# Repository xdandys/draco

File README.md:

Draco
==========

Draco is opensource HW&SW UAV flight controller board. It was primary designed for my needs, but anybody can manufacture it, use it or modify it. If you would like to own one, you can contact me. 

It has two MCUs on it. The smaller one is used for OSD. The bigger one is running [TauLabs][1] flight code.

###Features###
* main MCU STM32F4, MCU for OSD STM32F303CC
* 32MBit serial flash
* MPU9250 in SPI mode
* MS5611 in SPI mode
* CAN bus transceiver
* microSD slot via SDIO
* 4x A/D inputs
* slot for telemetry module (XBee or PirateBee)
* half-duplex inverted serial line for new FrSky S.PORT telemetry bus
* GPS port with power, UART and I2C for external compass
* 2x extension port with UART/I2C and GPIOs
* extension SPI port
* dedicated sonar port with power and trigger+echo signals
* microUSB
* 12x PWM in/out + 1x S.BUS/CPPM pin on 2.54mm header
* 6x LEDs
* micro button
* OSD with resolution 320x240, automatic PAL/NTSC detection
* dimmensions: 62x47mm

###TauLabs###
Draco is currently one of the non-official TauLabs target. You can find ported code at [my fork][2]. There are still some things missing and I will probably add them in short time:

* support for microSD card logging
* support of FrSky S.PORT telemetry protocol
* micro button support

  [1]: http://taulabs.org/
  [2]: https://github.com/strnadda/TauLabs/tree/draco

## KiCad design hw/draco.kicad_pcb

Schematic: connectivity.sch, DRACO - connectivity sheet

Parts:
C1, C3, C5, C7, C8, C10, C12, C14, C15, C17, C43, C47, C48: 100nF; c_0603
C2, C4: 4.7uF; c_0805
C6, C13: 10uF; c_0805
C9: 1uF; c_0805
C11: 10nF; c_0603
C16: 22uF; c_0805
C18: 56nF; c_0603
C44: 510pF; c_0603
D1: PMEG6010CEH
D2: LED_RED; led_2.1x0.6
D3: LED_ORANGE; led_2.1x0.6
D4: LED_BLUE; led_2.1x0.6
D5: LED_GREEN; led_2.1x0.6
D9: MBRS130T3G
D10: 1SMB7.0AT3G
G1, G2, G3, G4, G5: DUMMY
L1: 10uH; r_0805
P1: CONN_13X3; pin_strip_13x3-90
P2, P3, P5, P7, P8, P9: CONN_4; picoblade_4-90
P4: MICROUSB; conn_usb_B_micro_smd-FCI
P6, P13: CONN_6; picoblade_6-90
P10: MICROSD; MICRO-SD-SOCKET-PP
P11: CONN_9; picoblade_9-90
P12: CONN_2; picoblade_2-90
P19, P20, P21, P22: CONN_1; 1pin
Q2: NTA4153NT1G
Q3: NTA4151PT1G
Q4, Q5, Q6, Q7: PDTC114EE; sc75
R1, R2, R3, R4, R5, R6, R7, R8, R9, R10, R11, R12, R13, R14, R25, R26, R33, R42, R43, R46, R48, R49, R50, R51, R63, R64, R65: 470R; r_0603
R15, R16: 22R; r_0603
R17: 120R; r_0805
R18, R19, R20, R21, R24, R29, R30, R66, R67: 39k; r_0603
R22: 82k; r_0603
R23: 12k; r_0603
R27, R28, R31, R32, R53, R60: 220R; r_0603
R34, R36, R37, R38: 39k; r_0402
R35: 1M; r_0402
R39: 681k; r_0603
R40, R41: 4.7k; r_0603
R44, R58, R59: 4k7; r_0603
R45, R47: 330R; r_0603
R52: 180R; r_0603
R68, R69: 75R; r_0603
R70: 390R; r_0603
R71: 620R; r_0603
SW1: STG719; sot23-6
U1: XBEE; xbee-smt
U2: LTC4411; sot23-5
U3: SN65HVD233; so-8
U4: ADP3338AKCZ-3.3; stabil_sot223_1
U5: LT1761-3.3; tsot-5
U6: EL1883; so-8
U11: SN74AHC1G86
U12: MAX4090

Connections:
+3.3V: C1.2, C3.1, C4.1, C6.1, C14.2, C16.1, C17.2, C43.2, C48.1, P10.4, Q3.2 (S), R34.2, R36.2, R37.2, R38.2, R40.2, R41.2, R44.2, R58.2, R59.2, R70.2, SW1.2 (Vcc), U1.1, U3.3 (Vcc), U4.OUT, U6.8 (Vdd), U11.5 (Vcc), U12.4 (Vcc), U12.5 (~SD); also elsewhere on the board
+3.3VADC: C11.1, C13.1, U5.5 (OUT); also elsewhere on the board
+5V: D9.1 (A), P1.2, P1.5, P1.8, P1.11, P1.14, P1.17, P1.20, P1.23, P1.26, P1.29, P1.32, P1.35, P1.38, P2.4, P3.4, P6.1, P7.4, P11.9, P13.1, R45.2, R47.2, R52.2, R53.2
AD0: C5.2, R22.2, R23.2; also elsewhere on the board
AD1: C7.2, R21.2, R24.2; also elsewhere on the board
AD2: C8.2, R20.2, R29.2; also elsewhere on the board
AD3: C10.2, R19.2, R30.2; also elsewhere on the board
CAN_RX: U3.4 (R); also elsewhere on the board
CAN_TX: U3.1 (D); also elsewhere on the board
EXTGPIO1: R65.2; also elsewhere on the board
EXTGPIO2: R64.2; also elsewhere on the board
EXTGPIO3: R63.2; also elsewhere on the board
EXTI2C_SCL: R27.2; also elsewhere on the board
EXTI2C_SDA: R28.2; also elsewhere on the board
EXTSPI_CS: R51.1; also elsewhere on the board
EXTSPI_MISO: R49.1; also elsewhere on the board
EXTSPI_MOSI: R48.1; also elsewhere on the board
EXTSPI_SCK: R50.1; also elsewhere on the board
EXTUART1_RX: R43.2; also elsewhere on the board
EXTUART1_TX: R42.2; also elsewhere on the board
EXTUART2_RX: R31.2, R58.1; also elsewhere on the board
EXTUART2_TX: R59.1, R60.2; also elsewhere on the board
F4_NRST: C12.2, P9.2; also elsewhere on the board
F4_SWCLK: P9.4; also elsewhere on the board
F4_SWDIO: P9.3; also elsewhere on the board
GND: C1.1, C2.2, C3.2, C4.2, C5.1, C6.2, C7.1, C8.1, C9.2, C10.1, C12.1, C13.2, C14.1, C16.2, C17.1, C18.1, C43.1, C44.1, C48.2, D10.1 (A), P1.1, P1.4, P1.7, P1.10, P1.13, P1.16, P1.19, P1.22, P1.25, P1.28, P1.31, P1.34, P1.37, P2.3, P3.3, P4.5, P6.2, P7.3, P8.1, P8.4, P9.1, P10.6, P10.GND, P11.8, P12.1, P13.2, Q2.2 (S), Q4.2 (E), Q5.2 (E), Q6.2 (E), Q7.2 (E), R23.1, R24.1, R29.1, R30.1, R35.1, R39.1, R66.1, R67.2, R68.1, SW1.3 (GND), U1.10, U2.2 (GND), U3.2 (GND), U3.8 (RS), U4.GND, U5.2 (GND), U6.4 (GND), U11.3 (Gnd), U12.2 (GND); also elsewhere on the board
GPS_RX: R25.2; also elsewhere on the board
GPS_TX: R26.2; also elsewhere on the board
LED_BLUE: Q6.1 (B); also elsewhere on the board
LED_GREEN: Q7.1 (B); also elsewhere on the board
LED_ORANGE: Q5.1 (B); also elsewhere on the board
LED_RED: Q4.1 (B); also elsewhere on the board
unnamed: C47.1, U12.3 (IN)
unnamed: R69.2, U12.1 (OUT), U12.6 (FB)
unnamed: C47.2, P8.3, R68.2
unnamed: P11.6, R64.1
unnamed: P11.7, R65.1
unnamed: D5.2 (K), Q7.3 (C)
unnamed: P1.3, R66.2, U11.1 (IN1)
unnamed: C15.2, U6.2 (COMP_IN)
unnamed: C15.1, C44.2, R71.1
unnamed: P8.2, SW1.5 (D)
unnamed: R69.1, R71.2, SW1.6 (S2)
unnamed: C2.1, D1.2 (K), D9.2 (K), D10.2 (K), L1.1, U2.5 (OUT), U4.IN
unnamed: P11.1, R42.1
unnamed: P5.1, R19.1
unnamed: P11.5, R63.1
unnamed: P11.2, R43.1
unnamed: P5.3, R21.1
unnamed: P5.4, R22.1
unnamed: P5.2, R20.1
unnamed: C11.2, U5.4 (BYP)
unnamed: P6.6, R25.1
unnamed: P6.5, R26.1
unnamed: P6.3, P11.4, R28.1, R40.1
unnamed: D1.1 (A), P4.1, R18.2, U2.1 (IN)
unnamed: C9.1, L1.2, U5.1 (IN)
unnamed: P4.2, R15.1
unnamed: P4.3, R16.1
unnamed: P3.1, R1.1
unnamed: P3.2, R2.1
unnamed: P2.2, R17.1, U3.6 (CANL)
unnamed: P2.1, R17.2, U3.7 (CANH)
unnamed: P1.18, R10.1
unnamed: P1.15, R11.1
unnamed: P1.12, R12.1
unnamed: P1.6, R14.1
unnamed: P1.36, R4.1
unnamed: P1.33, R5.1
unnamed: P1.30, R6.1
unnamed: P13.3, R51.2
unnamed: P1.24, R8.1
unnamed: P1.27, R7.1
unnamed: P1.21, R9.1
unnamed: P7.1, R60.1
unnamed: C18.2, R39.2, U6.6 (RSET)
unnamed: P7.2, R31.1
unnamed: P1.39, R3.1
unnamed: P6.4, P11.3, R27.1, R41.1
unnamed: P1.9, R13.1
unnamed: Q2.1 (G), Q3.3 (D), R46.1, R67.1
unnamed: P12.2 (PM), R46.2
unnamed: P13.6, R48.2
unnamed: P13.5, R49.2
unnamed: P13.4, R50.2
unnamed: R32.1, R33.1, R70.1, SW1.4 (S1)
unnamed: D2.1 (A), R45.1
unnamed: D4.1 (A), R52.1
unnamed: D3.1 (A), R47.1
unnamed: D3.2 (K), Q5.3 (C)
unnamed: D4.2 (K), Q6.3 (C)
unnamed: D2.2 (K), Q4.3 (C)
unnamed: D5.1 (A), R53.1
OSD_HSYNC: U6.7 (~HSYNC~); also elsewhere on the board
OSD_MISO_MASK: SW1.1 (SW); also elsewhere on the board
OSD_MOSI_VOUT: R32.2; also elsewhere on the board
OSD_SYNCOUT: R33.2; also elsewhere on the board
OSD_VSYNC: U6.3 (~VSYNC~); also elsewhere on the board
PWM1: R14.2; also elsewhere on the board
PWM2: R13.2; also elsewhere on the board
PWM3: R12.2; also elsewhere on the board
PWM4: R11.2; also elsewhere on the board
PWM5: R10.2; also elsewhere on the board
PWM6: R9.2; also elsewhere on the board
PWM7: R8.2; also elsewhere on the board
PWM8: R7.2; also elsewhere on the board
PWM9: R6.2; also elsewhere on the board
PWM10: R5.2; also elsewhere on the board
PWM11: R4.2; also elsewhere on the board
PWM12: R3.2; also elsewhere on the board
SBUS: U11.4 (OUT); also elsewhere on the board
SBUS_UART_INVERT: U11.2 (IN2); also elsewhere on the board
SDIO_CLK: P10.5; also elsewhere on the board
SDIO_CMD: P10.3, R36.1; also elsewhere on the board
SDIO_D0: P10.7, R37.1; also elsewhere on the board
SDIO_D1: P10.8, R38.1; also elsewhere on the board
SDIO_D2: P10.1, R34.1; also elsewhere on the board
SDIO_D3: P10.2, R35.2; also elsewhere on the board
SON_ECHO: R1.2; also elsewhere on the board
SON_TRIG: R2.2; also elsewhere on the board
SPORT_RX: Q2.3 (D), R44.1; also elsewhere on the board
SPORT_TX: Q3.1 (G); also elsewhere on the board
USBDM: R15.2; also elsewhere on the board
USBDP: R16.2; also elsewhere on the board
USBVB: R18.1; also elsewhere on the board
USB_ID: P4.4; also elsewhere on the board
XBEE_CTS: U1.12; also elsewhere on the board
XBEE_RX: U1.2; also elsewhere on the board
XBEE_TX: U1.3; also elsewhere on the board

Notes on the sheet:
Sonar
CAN bus
Extension port
GPS
SWD
S.PORT / S.BUS 2.0
SPI
LED front panel
OSD
VID_OUT VID_IN
UART_F3
Can be potentionaly fitted for I2C
Mechanical mount holes and drawings
Sync-tip clamp
LTC1411 alternative

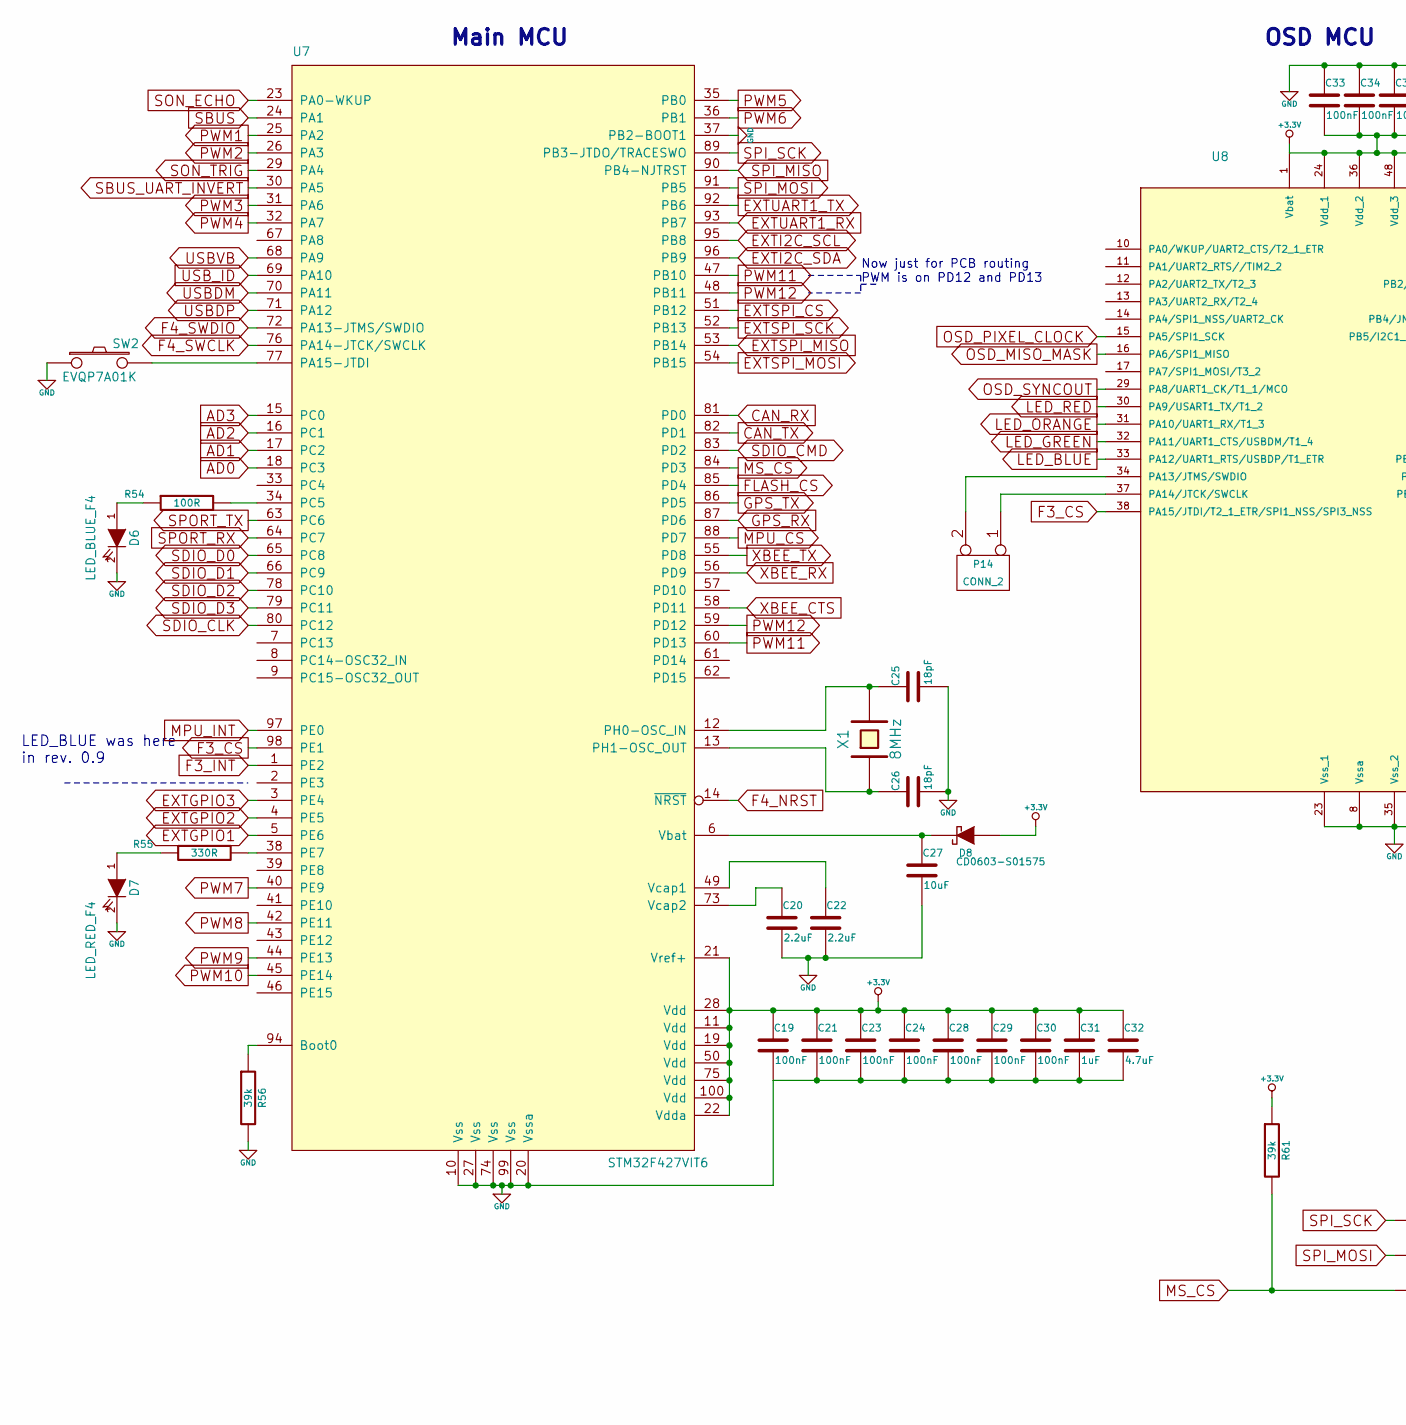
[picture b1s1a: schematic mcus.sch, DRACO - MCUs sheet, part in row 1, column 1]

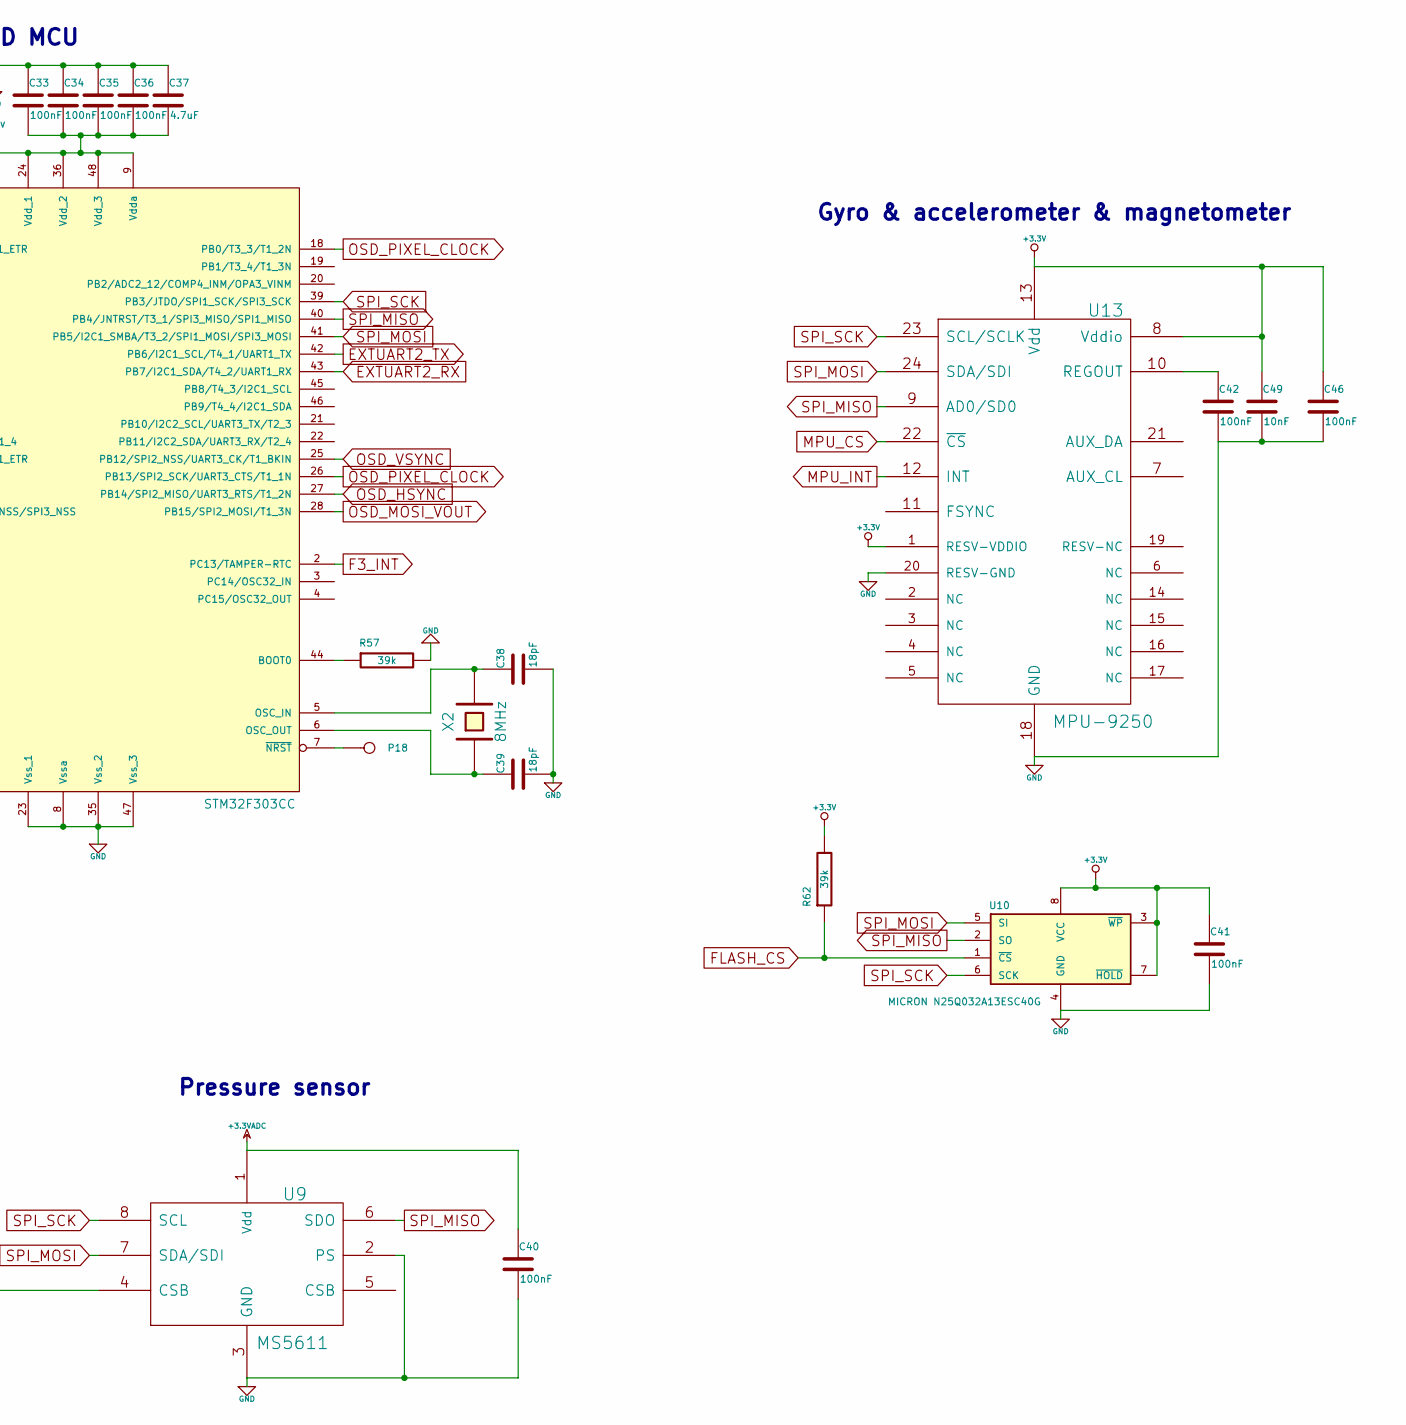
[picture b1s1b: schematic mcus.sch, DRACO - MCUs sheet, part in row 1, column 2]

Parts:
C19, C21, C23, C24, C28, C29, C30, C33, C34, C35, C36, C40, C41, C42, C46: 100nF; c_0603
C20, C22: 2.2uF; c_0805
C25, C26, C38, C39: 18pF; c_0603
C27: 10uF; c_0805
C31: 1uF; c_0603
C32: 4.7uF; c_0805
C37: 4.7uF; c_0603
C49: 10nF; c_0603
D6: LED_BLUE_F4; Led_0603
D7: LED_RED_F4; Led_0603
D8: CD0603-S01575; r_0603
P14: CONN_2
P18: CONN_1; testpoint_pad
R54: 100R; r_0603
R55: 330R; r_0603
R56, R57, R61, R62: 39k; r_0603
SW2: EVQP7A01K
U7: STM32F427VIT6; TQFP-100
U8: STM32F303CC; lqfp48
U9: MS5611
U10: MICRON N25Q032A13ESC40G
U13: MPU-9250
X1, X2: 8MHz; crystal_smd_5x3.2mm

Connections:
+3.3V: C19.1, C21.1, C23.1, C24.1, C28.1, C29.1, C30.1, C31.1, C32.1, C33.2, C34.2, C35.2, C36.2, C37.2, C41.1, C46.1, C49.1, D8.1 (A), R61.1, R62.2, U7.11 (Vdd), U7.19 (Vdd), U7.21 (Vref+), U7.22 (Vdda), U7.28 (Vdd), U7.50 (Vdd), U7.75 (Vdd), U7.100 (Vdd), U8.1 (Vbat), U8.9 (Vdda), U8.24 (Vdd_1), U8.36 (Vdd_2), U8.48 (Vdd_3), U10.3 (~WP), U10.7 (~HOLD), U10.8 (VCC), U13.1 (RESV-VDDIO), U13.8 (Vddio), U13.13 (Vdd); also elsewhere on the board
+3.3VADC: C40.1, U9.1 (Vdd); also elsewhere on the board
AD0: U7.18 (PC3); also elsewhere on the board
AD1: U7.17 (PC2); also elsewhere on the board
AD2: U7.16 (PC1); also elsewhere on the board
AD3: U7.15 (PC0); also elsewhere on the board
CAN_RX: U7.81 (PD0); also elsewhere on the board
CAN_TX: U7.82 (PD1); also elsewhere on the board
EXTGPIO1: U7.5 (PE6); also elsewhere on the board
EXTGPIO2: U7.4 (PE5); also elsewhere on the board
EXTGPIO3: U7.3 (PE4); also elsewhere on the board
EXTI2C_SCL: U7.95 (PB8); also elsewhere on the board
EXTI2C_SDA: U7.96 (PB9); also elsewhere on the board
EXTSPI_CS: U7.51 (PB12); also elsewhere on the board
EXTSPI_MISO: U7.53 (PB14); also elsewhere on the board
EXTSPI_MOSI: U7.54 (PB15); also elsewhere on the board
EXTSPI_SCK: U7.52 (PB13); also elsewhere on the board
EXTUART1_RX: U7.93 (PB7); also elsewhere on the board
EXTUART1_TX: U7.92 (PB6); also elsewhere on the board
EXTUART2_RX: U8.43 (PB7/I2C1_SDA/T4_2/UART1_RX); also elsewhere on the board
EXTUART2_TX: U8.42 (PB6/I2C1_SCL/T4_1/UART1_TX); also elsewhere on the board
F3_CS: U7.98 (PE1), U8.38 (PA15/JTDI/T2_1_ETR/SPI1_NSS/SPI3_NSS)
F3_INT: U7.1 (PE2), U8.2 (PC13/TAMPER-RTC)
F4_NRST: U7.14 (~NRST~); also elsewhere on the board
F4_SWCLK: U7.76 (PA14-JTCK/SWCLK); also elsewhere on the board
F4_SWDIO: U7.72 (PA13-JTMS/SWDIO); also elsewhere on the board
FLASH_CS: R62.1, U7.85 (PD4), U10.1 (~CS)
GND: C19.2, C20.2, C21.2, C22.2, C23.2, C24.2, C25.2, C26.2, C27.2, C28.2, C29.2, C30.2, C31.2, C32.2, C33.1, C34.1, C35.1, C36.1, C37.1, C38.2, C39.2, C40.2, C41.2, C42.2, C46.2, C49.2, D6.2 (K), D7.2 (K), R56.2, R57.2, SW2.1, U7.10 (Vss), U7.20 (Vssa), U7.27 (Vss), U7.37 (PB2-BOOT1), U7.74 (Vss), U7.99 (Vss), U8.8 (Vssa), U8.23 (Vss_1), U8.35 (Vss_2), U8.47 (Vss_3), U9.2 (PS), U9.3 (GND), U10.4 (GND), U13.18 (GND), U13.20 (RESV-GND); also elsewhere on the board
GPS_RX: U7.87 (PD6); also elsewhere on the board
GPS_TX: U7.86 (PD5); also elsewhere on the board
LED_BLUE: U8.33 (PA12/UART1_RTS/USBDP/T1_ETR); also elsewhere on the board
LED_GREEN: U8.32 (PA11/UART1_CTS/USBDM/T1_4); also elsewhere on the board
LED_ORANGE: U8.31 (PA10/UART1_RX/T1_3); also elsewhere on the board
LED_RED: U8.30 (PA9/USART1_TX/T1_2); also elsewhere on the board
MPU_CS: U7.88 (PD7), U13.22 (~CS~)
MPU_INT: U7.97 (PE0), U13.12 (INT)
MS_CS: R61.2, U7.84 (PD3), U9.4 (CSB)
unnamed: C20.1, U7.73 (Vcap2)
unnamed: C22.1, U7.49 (Vcap1)
unnamed: C27.1, D8.2 (K), U7.6 (Vbat)
unnamed: R57.1, U8.44 (BOOT0)
unnamed: P18.1, U8.7 (~NRST~)
unnamed: R55.2, U7.38 (PE7)
unnamed: R56.1, U7.94 (Boot0)
unnamed: C42.1, U13.10 (REGOUT)
unnamed: D7.1 (A), R55.1
unnamed: R54.2, U7.34 (PC5)
unnamed: D6.1 (A), R54.1
unnamed: SW2.2, U7.77 (PA15-JTDI)
unnamed: P14.2 (PM), U8.34 (PA13/JTMS/SWDIO)
unnamed: P14.1, U8.37 (PA14/JTCK/SWCLK)
unnamed: C39.1, U8.6 (OSC_OUT), X2.1
unnamed: C38.1, U8.5 (OSC_IN), X2.2
unnamed: C25.1, U7.12 (PH0-OSC_IN), X1.2
unnamed: C26.1, U7.13 (PH1-OSC_OUT), X1.1
OSD_HSYNC: U8.27 (PB14/SPI2_MISO/UART3_RTS/T1_2N); also elsewhere on the board
OSD_MISO_MASK: U8.16 (PA6/SPI1_MISO); also elsewhere on the board
OSD_MOSI_VOUT: U8.28 (PB15/SPI2_MOSI/T1_3N); also elsewhere on the board
OSD_PIXEL_CLOCK: U8.15 (PA5/SPI1_SCK), U8.18 (PB0/T3_3/T1_2N), U8.26 (PB13/SPI2_SCK/UART3_CTS/T1_1N)
OSD_SYNCOUT: U8.29 (PA8/UART1_CK/T1_1/MCO); also elsewhere on the board
OSD_VSYNC: U8.25 (PB12/SPI2_NSS/UART3_CK/T1_BKIN); also elsewhere on the board
PWM1: U7.25 (PA2); also elsewhere on the board
PWM2: U7.26 (PA3); also elsewhere on the board
PWM3: U7.31 (PA6); also elsewhere on the board
PWM4: U7.32 (PA7); also elsewhere on the board
PWM5: U7.35 (PB0); also elsewhere on the board
PWM6: U7.36 (PB1); also elsewhere on the board
PWM7: U7.40 (PE9); also elsewhere on the board
PWM8: U7.42 (PE11); also elsewhere on the board
PWM9: U7.44 (PE13); also elsewhere on the board
PWM10: U7.45 (PE14); also elsewhere on the board
PWM11: U7.47 (PB10), U7.60 (PD13); also elsewhere on the board
PWM12: U7.48 (PB11), U7.59 (PD12); also elsewhere on the board
SBUS: U7.24 (PA1); also elsewhere on the board
SBUS_UART_INVERT: U7.30 (PA5); also elsewhere on the board
SDIO_CLK: U7.80 (PC12); also elsewhere on the board
SDIO_CMD: U7.83 (PD2); also elsewhere on the board
SDIO_D0: U7.65 (PC8); also elsewhere on the board
SDIO_D1: U7.66 (PC9); also elsewhere on the board
SDIO_D2: U7.78 (PC10); also elsewhere on the board
SDIO_D3: U7.79 (PC11); also elsewhere on the board
SON_ECHO: U7.23 (PA0-WKUP); also elsewhere on the board
SON_TRIG: U7.29 (PA4); also elsewhere on the board
SPI_MISO: U7.90 (PB4-NJTRST), U8.40 (PB4/JNTRST/T3_1/SPI3_MISO/SPI1_MISO), U9.6 (SDO), U10.2 (SO), U13.9 (AD0/SD0)
SPI_MOSI: U7.91 (PB5), U8.41 (PB5/I2C1_SMBA/T3_2/SPI1_MOSI/SPI3_MOSI), U9.7 (SDA/SDI), U10.5 (SI), U13.24 (SDA/SDI)
SPI_SCK: U7.89 (PB3-JTDO/TRACESWO), U8.39 (PB3/JTDO/SPI1_SCK/SPI3_SCK), U9.8 (SCL), U10.6 (SCK), U13.23 (SCL/SCLK)
SPORT_RX: U7.64 (PC7); also elsewhere on the board
SPORT_TX: U7.63 (PC6); also elsewhere on the board
USBDM: U7.70 (PA11); also elsewhere on the board
USBDP: U7.71 (PA12); also elsewhere on the board
USBVB: U7.68 (PA9); also elsewhere on the board
USB_ID: U7.69 (PA10); also elsewhere on the board
XBEE_CTS: U7.58 (PD11); also elsewhere on the board
XBEE_RX: U7.56 (PD9); also elsewhere on the board
XBEE_TX: U7.55 (PD8); also elsewhere on the board

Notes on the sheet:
Pressure sensor
Gyro & accelerometer & magnetometer
OSD MCU
Main MCU
Now just for PCB routing PWM is on PD12 and PD13
LED_BLUE was here in rev. 0.9

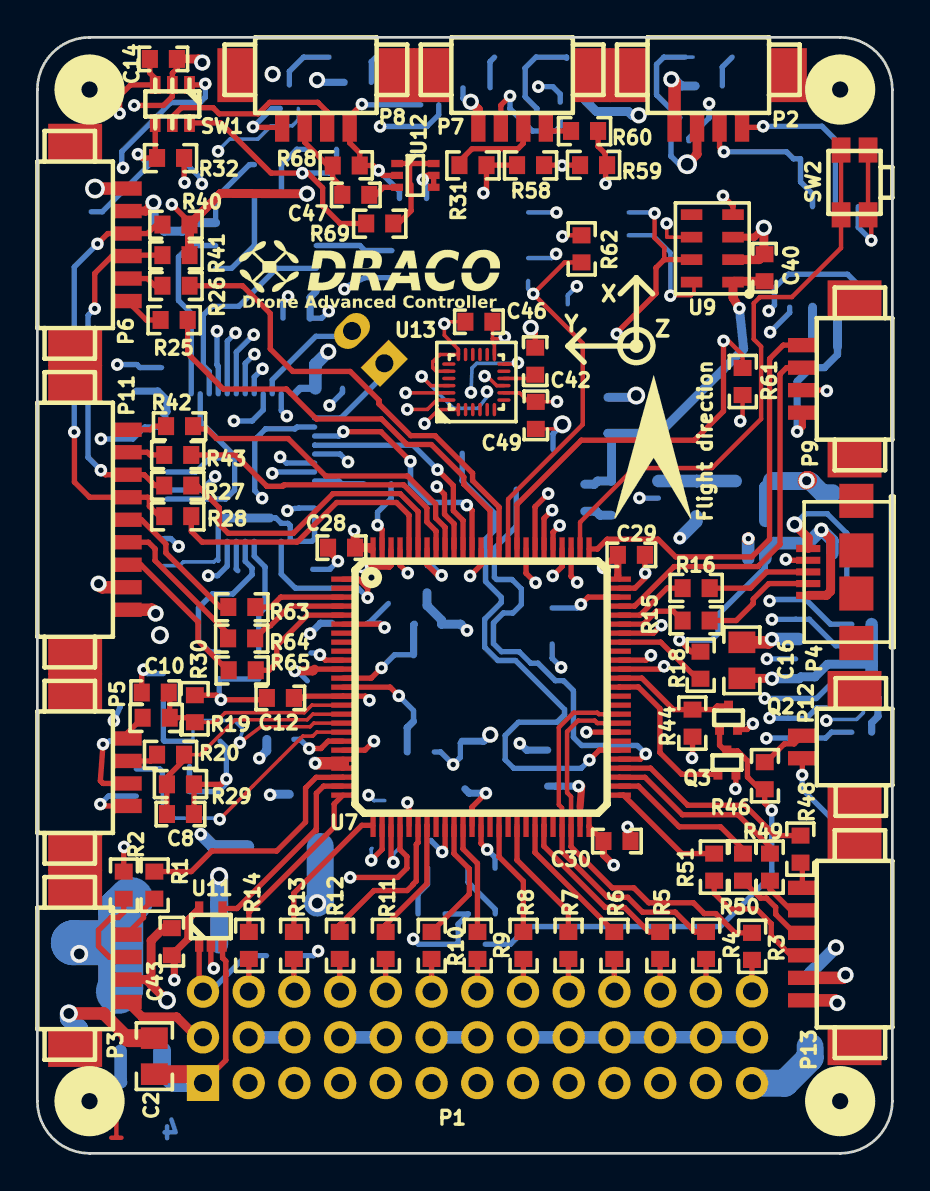
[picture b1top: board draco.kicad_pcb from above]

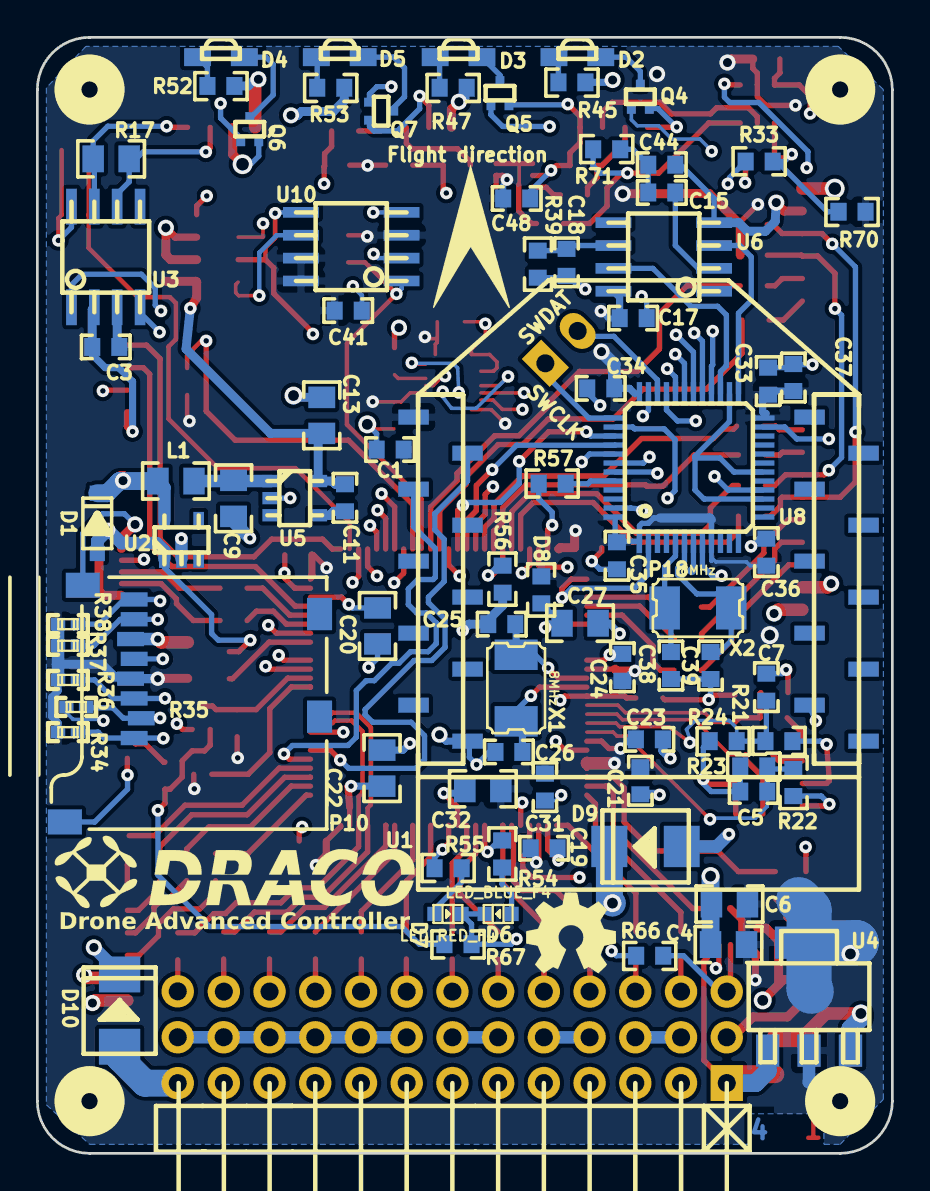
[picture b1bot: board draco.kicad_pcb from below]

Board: 4 copper layers, 47.5 x 62.0 mm, 177 parts (87 on the bottom side), 157 nets.

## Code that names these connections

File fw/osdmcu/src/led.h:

/*
    DRACO - Copyright (C) 2013-2014 Daniel Strnad
                 
    This file is part of DRACO project.

    DRACO is free software; you can redistribute it and/or modify
    it under the terms of the GNU General Public License as published by
    the Free Software Foundation; either version 3 of the License, or
    (at your option) any later version.

    DRACO is distributed in the hope that it will be useful,
    but WITHOUT ANY WARRANTY; without even the implied warranty of
    MERCHANTABILITY or FITNESS FOR A PARTICULAR PURPOSE.  See the
    GNU General Public License for more details.

    You should have received a copy of the GNU General Public License
    along with this program.  If not, see <http://www.gnu.org/licenses/>.

*/

/**
 * @file    led.h
 * @brief   LEDs controlling code
 *
 */

#ifndef LED_H_
#define LED_H_

#define LED_RED                 0
#define LED_GREEN               1
#define LED_BLUE                2
#define LED_ORANGE              3

#define LED_MODE_OFF            0
#define LED_MODE_ON             1
#define LED_MODE_BLINK_SLOW     2
#define LED_MODE_BLINK_FAST     3

void ledInit(void);
void ledControl(uint8_t led, uint8_t mode);

#endif /* LED_H_ */

/** @} */

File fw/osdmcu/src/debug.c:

/*
    DRACO - Copyright (C) 2013-2014 Daniel Strnad

    This file is part of DRACO project.

    DRACO is free software; you can redistribute it and/or modify
    it under the terms of the GNU General Public License as published by
    the Free Software Foundation; either version 3 of the License, or
    (at your option) any later version.

    DRACO is distributed in the hope that it will be useful,
    but WITHOUT ANY WARRANTY; without even the implied warranty of
    MERCHANTABILITY or FITNESS FOR A PARTICULAR PURPOSE.  See the
    GNU General Public License for more details.

    You should have received a copy of the GNU General Public License
    along with this program.  If not, see <http://www.gnu.org/licenses/>.
*/
/**
 * @file    debug.c
 * @brief   debugging routines
 *
 */

#include <stm32f30x.h>
#include <stm32f30x_rcc.h>
#include <stm32f30x_usart.h>
#include <stm32f30x_gpio.h>
#include <stdint.h>
#include "debug.h"
#include "board.h"
#include <stdarg.h>
#include <string.h>
#include <stdio.h>
#include "stdlib.h"

#define DEBUG_USE_SEMIHOSTING
#define DEBUG_BAUDRATE  115200

#ifdef DEBUG_USART2_PA2_PA3
    #define DEBUG_USART2
    #define USART_DBG USART2
    #define USART_FREQ  SYSCLK_FREQ
#elif defined DEBUG_USART1_PA9_PA10
    #define DEBUG_USART1
    #define USART_DBG USART1
    #define USART_FREQ  (SYSCLK_FREQ)
#endif

void DebugInit(void)
{
#ifdef DEBUG_USART2_PA2_PA3
    RCC->AHBENR |= RCC_AHBENR_GPIOAEN;
    GPIOA->MODER |= GPIO_MODER_MODER2_1 | GPIO_MODER_MODER3_1;
    GPIOA->AFR[0] &= ~(GPIO_AFRL_AFRL2 | GPIO_AFRL_AFRL3);
    GPIOA->AFR[0] |= ((1 << 8) | (1 << 12));                   // assign PA2, PA3 alternate function to USART2
    RCC->APB1ENR |= RCC_APB1ENR_USART2EN;
    USART_DBG->BRR = USART_FREQ / DEBUG_BAUDRATE;
    USART_DBG->CR1 = USART_CR1_TE | USART_CR1_RE | USART_CR1_UE;

    dbgready = 1;

#elif defined DEBUG_USART1_PA9_PA10
    RCC->AHBENR |= RCC_AHBENR_GPIOAEN;
    GPIOA->MODER |= GPIO_MODER_MODER9_1 | GPIO_MODER_MODER10_1;
    GPIOA->AFR[1] &= ~(GPIO_AFRH_AFRH1 | GPIO_AFRH_AFRH2);
    GPIOA->AFR[1] |= ((7 << 4) | (7 << 8));                   // assign PA9, PA10 alternate function to USART1
    RCC->APB2ENR |= RCC_APB2ENR_USART1EN;
    USART_DBG->BRR = USART_FREQ / DEBUG_BAUDRATE;
    USART_DBG->CR1 = USART_CR1_TE | USART_CR1_RE | USART_CR1_UE;

    dbgready = 1;

#endif

}

int shwrites(const char *str)
{
    static uint32_t args[3];
    uint32_t size = strlen(str);
    args[0] = 1;
    args[1] = (uint32_t)str;
    args[2] = size;

    // return -1;
    if ((CoreDebug->DHCSR & 1) == 0)
        return -1;

    asm volatile("mov r0, #5\n"
        "mov r1, %0\n"
        "bkpt 0x00ab"  : : "r"(args) : "r0", "r1");
    return args[2];
}

#ifndef DEBUG_USE_SEMIHOSTING
void DebugSendString(const char *str)
{
#if defined DEBUG_USART1_PA9_PA10 || defined DEBUG_USART2_PA2_PA3
    uint16_t i = 0;
    if (!dbgready) DebugInit();
    for(i=0;str[i]!=0x00;i++)
    {
        while((USART_DBG->ISR & USART_ISR_TXE) == 0);
        USART_DBG->TDR = str[i];
    }
    //while ((USART_DBG->SR & USART_SR_TC) == 0);
#endif
}

void DebugPutChar(char c)
{
#if defined DEBUG_USART1_PA9_PA10 || defined DEBUG_USART2_PA2_PA3
    if (!dbgready) DebugInit();
    while((USART_DBG->ISR & USART_ISR_TXE) == 0);
    USART_DBG->TDR = c;
#endif
}
#else
static char shwrbuff[128];
static uint32_t shwrbuffCount = 0;

void DebugPutChar(char c)
{
    shwrbuff[shwrbuffCount++] = c;

    if ((shwrbuffCount > (sizeof(shwrbuff) -2)) || (c == '\n') || (c == 0))  {
        shwrbuff[shwrbuffCount] = 0;
        shwrbuffCount = 0;
        shwrites(shwrbuff);
    }
}

void DebugSendString(const char *msg)
{
    shwrites(msg);
}
#endif

void _dhexprint(const char *file, const char *function, const uint8_t *dataPointer, uint16_t len)
{
    uint8_t i;
    uint16_t pos=0;
    while(1)
    {
        DebugPrintf(DEBUG_STR_FORMAT "%04x ",getElapsedMs() / 1000, getElapsedMs() % 1000, file, function, pos);
        for (i=0;i<16;i++) {
            if (pos<len) DebugPrintf("%02x ", dataPointer[pos++]);
        }
        DebugPrintf("\r\n");
        if(pos>=len) break;
    }
}

static void printchar(char **str, int c)
{
    if (str) {
        **str = c;
        ++(*str);
    }
    else {
        DebugPutChar((char) c);
    }
}

#define PAD_RIGHT 1
#define PAD_ZERO 2

static int prints(char **out, const char *string, int width, int pad)
{
    int pc = 0, padchar = ' ';

    if (width > 0) {
        int len = 0;
        const char *ptr;
        for (ptr = string; *ptr; ++ptr) ++len;
        if (len >= width) width = 0;
        else width -= len;
        if (pad & PAD_ZERO) padchar = '0';
    }
    if (!(pad & PAD_RIGHT)) {
        for ( ; width > 0; --width) {
            printchar (out, padchar);
            ++pc;
        }
    }
    for ( ; *string ; ++string) {
        printchar (out, *string);
        ++pc;
    }
    for ( ; width > 0; --width) {
        printchar (out, padchar);
        ++pc;
    }

    return pc;
}

/* the following should be enough for 32 bit int */
#define PRINT_BUF_LEN 12

static int printi(char **out, int i, int b, int sg, int width, int pad, int letbase)
{
    char print_buf[PRINT_BUF_LEN];
    char *s;
    int t, neg = 0, pc = 0;
    unsigned int u = i;

    if (i == 0) {
        print_buf[0] = '0';
        print_buf[1] = '\0';
        return prints (out, print_buf, width, pad);
    }

    if (sg && b == 10 && i < 0) {
        neg = 1;
        u = -i;
    }

    s = print_buf + PRINT_BUF_LEN-1;
    *s = '\0';

    while (u) {
        t = u % b;
        if( t >= 10 )
            t += letbase - '0' - 10;
        *--s = t + '0';
        u /= b;
    }

    if (neg) {
        if( width && (pad & PAD_ZERO) ) {
            printchar (out, '-');
            ++pc;
            --width;
        }
        else {
            *--s = '-';
        }
    }

    return pc + prints (out, s, width, pad);
}

static int print(char **out, const char *format, va_list args )
{
    int width, pad;
    int pc = 0;
    char scr[2];

    for (; *format != 0; ++format) {
        if (*format == '%') {
            ++format;
            width = pad = 0;
            if (*format == '\0') break;
            if (*format == '%') goto out;
            if (*format == '-') {
                ++format;
                pad = PAD_RIGHT;
            }
            while (*format == '0') {
                ++format;
                pad |= PAD_ZERO;
            }
            for ( ; *format >= '0' && *format <= '9'; ++format) {
                width *= 10;
                width += *format - '0';
            }
            if( *format == 's' ) {
                char *s = (char *)va_arg( args, int );
                pc += prints (out, s?s:"(null)", width, pad);
                continue;
            }
            if( *format == 'd' ) {
                pc += printi (out, va_arg( args, int ), 10, 1, width, pad, 'a');
                continue;
            }
            if( *format == 'x' ) {
                pc += printi (out, va_arg( args, int ), 16, 0, width, pad, 'a');
                continue;
            }
            if( *format == 'X' ) {
                pc += printi (out, va_arg( args, int ), 16, 0, width, pad, 'A');
                continue;
            }
            if( *format == 'u' ) {
                pc += printi (out, va_arg( args, int ), 10, 0, width, pad, 'a');
                continue;
            }
            if( *format == 'c' ) {
                /* char are converted to int then pushed on the stack */
                scr[0] = (char)va_arg( args, int );
                scr[1] = '\0';
                pc += prints (out, scr, width, pad);
                continue;
            }
        }
        else {
        out:
            printchar (out, *format);
            ++pc;
        }
    }
    if (out) **out = '\0';
    va_end( args );
    return pc;
}

int DebugPrintf(const char *format, ...)
{
        va_list args;

        va_start( args, format );
        return print( 0, format, args );
}

int sprintf(char *out, const char *format, ...)
{
        va_list args;

        va_start( args, format );
        return print( &out, format, args );
}

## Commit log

2013-05-08 Pridany datasheety k obvodum, zalozen projekt, nove soucastky v dandys.lib
2013-05-08 added datasheet for Gmm-g9 module
2013-11-17 Commited 0.9 rev
2014-01-26 Just cosmetic changes for eye-candy, no changes in board layout
2014-01-26 schematic: BJTs in S.BUS and S.PORT inverters replaced by MOSFETs (faster switching speed)
2014-02-11 Pixel clock (SPI SCK) connected to PB0 (TIM1) in schematic This will enable us to use both SPIs in slave mode with fine pixel clock tuning by timer TIM1
2014-02-15 schematics: preparations for board rev. 1.0 MPU-6000 and HMC5893 replaced by single chip solution MPU-9250 Added video sync tip clamping MAX4090
2014-02-17 kicad libs: added walter w_switch library
2014-02-19 HW board revision 1.0
    - HMC5983 and MPU6000 replaced by MPU9250 on SPI bus
    - added video sync-tip clamping and buffer circuit MAX4090
    - added shottky diode D1 as optional alternative for ideal diode circuit LTC4411
    - SPI pixel clock generation now also connected to timer output for more fine clock tuning to be possible
    - PWM11 and PWM12 signals now switched to PD12 and PD13 to avoid collision of timer usage for sonar echo measurement
    - SMT32F4 LEDs moved to more suitable place on the board and blue LED switched to GPIO PC5 (was PE3)
2014-05-11 Updated assembly csv and pdf schematic
2014-05-17 Another big messy early commit
2014-05-17 Removed kicad backup file
2014-06-02 osdmcu: added SPI communication transport layer
2014-06-08 Polished OSD SPI driver and added PAL/NTSC autodetection
2014-06-08 added HUD layer, communication commands and minor improvements
2014-06-08 spicomm: added SYNC frame
2014-06-08 added command for set HUD units (metric/imperial)
2014-06-08 Fixed typos
2014-06-08 fixed bug in GPS widget; updated gitignore
2014-06-09 spicomm: fixed processing of SYNC frame
2014-06-09 fix: prepare _next_ line in HSYNC interrupt
2014-06-14 added board images
2014-06-14 added another board image
2014-07-09 hud: allow attitude indicator to use whole horizontal screen resolution for pitch indication
2014-07-10 leds: fixed duty cycle calculation
2014-07-24 osd: make tv system selectable
2014-07-27 hud: correct negative value displaying in wgVerticalGauge
2014-07-27 hud: fixed bug in stopwatch pause
2014-07-27 hud: fixed displaying value in wgVerticalGauge again (Yes, I'm retarded idiot)
2014-07-29 hud wgtext: fixed weird blinking
2014-09-24 hw: added diode from servo +5V to +3.3V stabs, TSV protection diode
2014-09-24 hw: SBUS inverting FET replaced by XOR gate (controllable inverter)
2014-09-25 hw: added series resistor to USB VBUS sense pin
2014-09-25 hw: add chroma filter to sync separator, removed unused CSYNC signal
2014-09-26 hw: rev 1.10, export for eurocircuits
2014-10-27 hw: updated BOM for rev 1.10
2014-11-16 style, white spaces and comments fix
2014-11-19 hw: USB Vbus resistor value lowered to 18k
2014-11-22 changed versioning system to git describe
2014-11-22 compiling environment splitted to the bootloader and firmware targets
2014-11-22 removed Makefile from .gitignore
2014-11-22 ensure video signal passthrough while in bootloader
2014-11-22 added flash memory operation code
2014-11-22 communication with bootloader via word in SRAM
2014-11-22 flashupdate: corrected file headers
2014-11-22 bootloader is now able to boot (but nothing else)
2014-11-23 bootloader: first version of bootloader code
2014-11-23 bootloader: fixed time measuring issue with entering to bootloader, minor name changes
2014-11-23 bootloader: fixed blockSize bug in chunkread
2014-11-29 fixed whitespaces
2015-03-22 mechanical: added printable 3D models for draco box
2015-07-18 added openocd flash script
